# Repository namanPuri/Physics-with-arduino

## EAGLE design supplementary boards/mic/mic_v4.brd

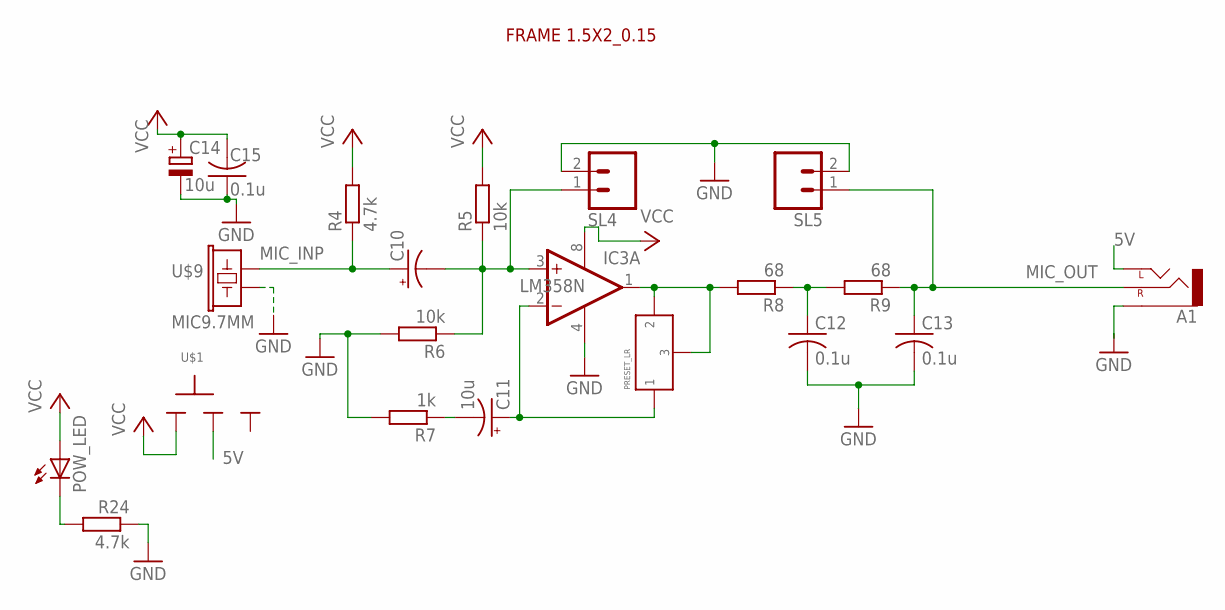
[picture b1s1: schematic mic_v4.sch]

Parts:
A1: AUX-CONNECTOR_CEDT_JANUARY_2015_V5_AUDIO-JACKPTH; AUX-CONNECTOR_CEDT_JANUARY_2015_V5_AUDIO-JACK
C10: CPOL-USE2.5-5; E2,5-5
C11, C14: 10u; E2,5-5
C12, C13, C15: 0.1u; C025-024X044
IC3: LM358N; DIL08
POW_LED: LED3MM
R4, R24: 4.7k; 0204/7
R5, R6: 10k; 0204/7
R7: 1k; 0204/7
R8, R9: 68; 0204/7
SL4, SL5: M02; 02P
U$1: SLIDESWITCH-BIG; BIGSWITCH
U$2: FRAME_1.5X2_RAD_0.15
U$6: PRESET_LR
U$9: MIC9.7MM; MIC-9.7MM

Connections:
5V: A1.TIP (LEFT), U$1.2
GND: A1.SLEEVE, C12.2, C13.2, C14.-, C15.1, IC3.4 (V-), R6.2, R7.2, R24.1, SL4.2, SL5.2, U$9.2
MIC_INP: C10.+, R4.1, U$9.1
MIC_OUT: A1.RING (RIGHT), C13.1, R9.1, SL5.1
unnamed: IC3.1 (OUT), R8.2, U$6.P$2 (2), U$6.P$3 (3)
unnamed: C12.1, R8.1, R9.2
unnamed: C11.-, R7.1
unnamed: POW_LED.K (C), R24.2
unnamed: C10.-, IC3.3 (+IN), R5.1, R6.1, SL4.1
unnamed: C11.+, IC3.2 (-IN), U$6.P$1 (1)
VCC: C14.+, C15.2, IC3.8 (V+), POW_LED.A, R4.2, R5.2, U$1.1

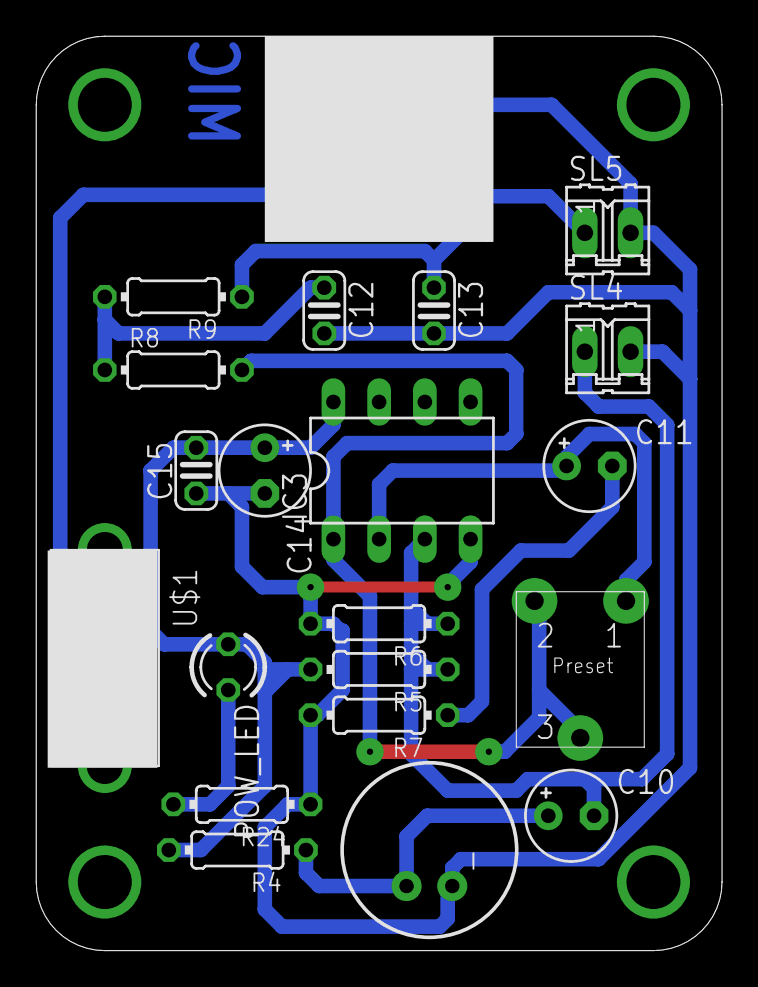
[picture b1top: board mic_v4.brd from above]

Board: 2 copper layers, 38.1 x 50.8 mm, 22 parts (0 on the bottom side), 11 nets.

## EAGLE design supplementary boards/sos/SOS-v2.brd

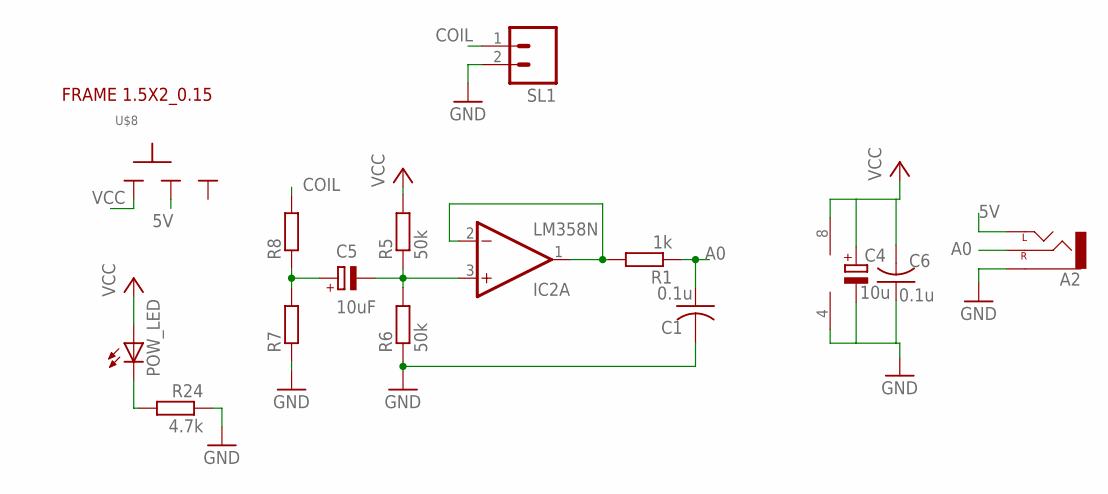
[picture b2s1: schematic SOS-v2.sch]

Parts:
A2: AUX-CONNECTOR_CEDT_JANUARY_2015_V5_AUDIO-JACKPTH; AUX-CONNECTOR_CEDT_JANUARY_2015_V5_AUDIO-JACK
C1, C6: 0.1u; C025-024X044
C4: 10u; E2,5-5
C5: 10uF; E2,5-6
IC2: LM358N; DIL08
POW_LED: LED3MM
R1: 1k; 0204/7
R5, R6: 50k; 0204/7
R7, R8: R-EU_0204/7; 0204/7
R24: 4.7k; 0204/7
SL1: M02; 02P
U$1: FRAME_1.5X2_RAD_0.15
U$8: SLIDESWITCH-BIG; BIGSWITCH

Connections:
5V: A2.TIP (LEFT), U$8.2
A0: A2.RING (RIGHT), C1.1, R1.1
CLAMP_SIGNAL: C5.-, IC2.3 (+IN), R5.1, R6.2
COIL: R8.2, SL1.1
GND: A2.SLEEVE, C1.2, C4.-, C6.1, IC2.4 (V-), R6.1, R7.1, R24.1, SL1.2
unnamed: C5.+, R7.2, R8.1
unnamed: IC2.1 (OUT), IC2.2 (-IN), R1.2
unnamed: POW_LED.K (C), R24.2
VCC: C4.+, C6.2, IC2.8 (V+), POW_LED.A, R5.2, U$8.1

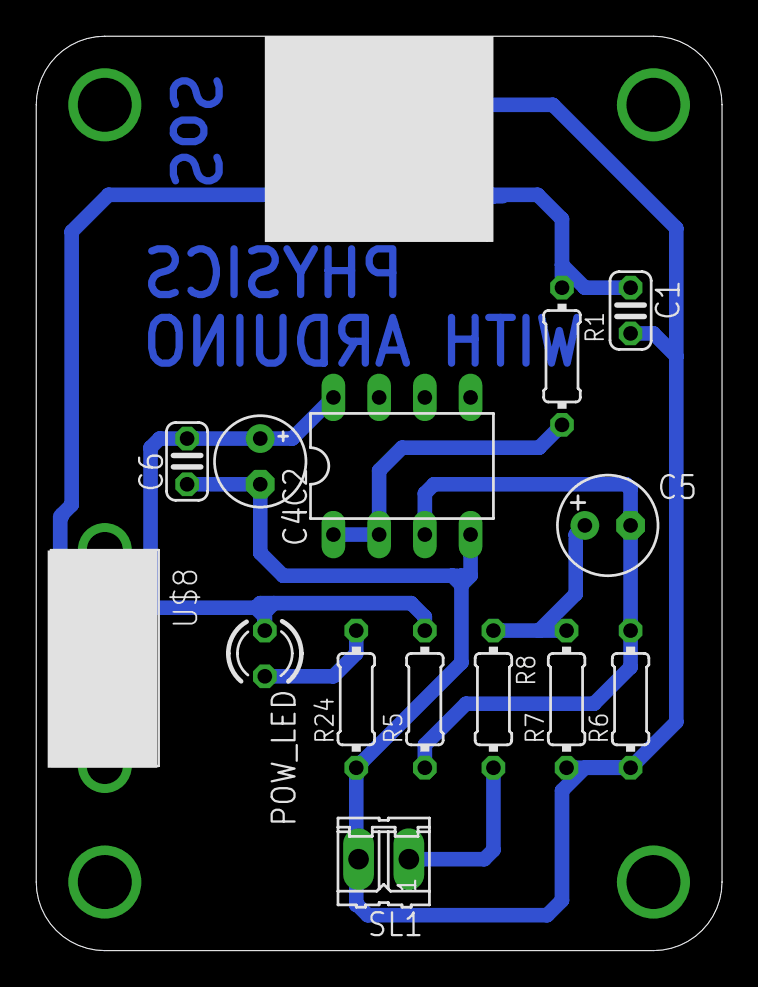
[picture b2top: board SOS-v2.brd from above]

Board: 2 copper layers, 38.1 x 50.8 mm, 16 parts (0 on the bottom side), 9 nets.

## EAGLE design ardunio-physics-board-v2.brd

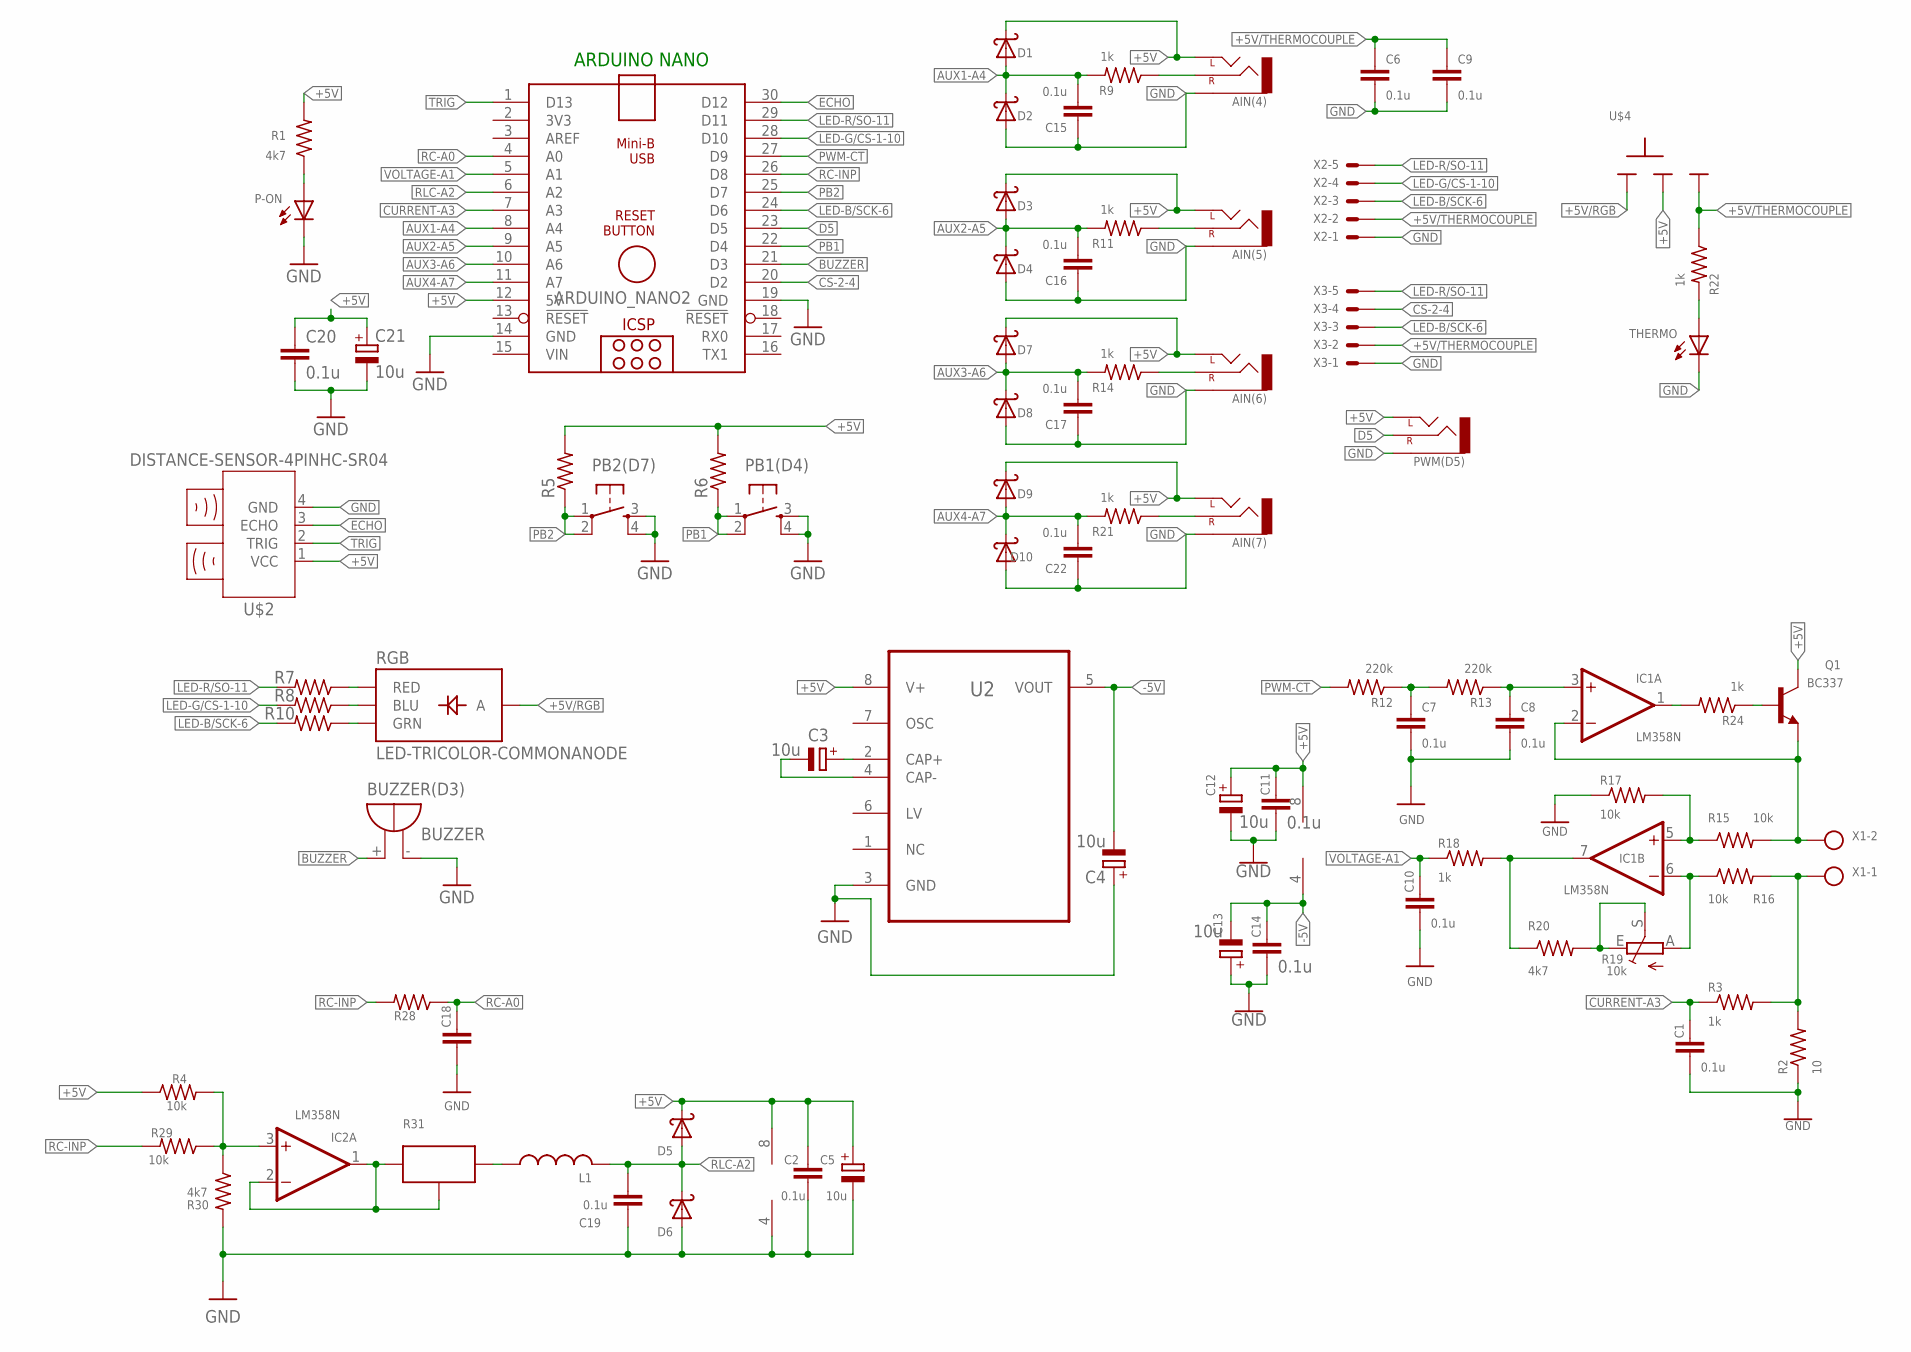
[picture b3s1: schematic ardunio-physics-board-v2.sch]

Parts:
AIN(4), AIN(5), AIN(6), AIN(7): AUX-CONNECTOR_CEDT_JANUARY_2015_V5_AUDIO-JACKPTH; AUX-CONNECTOR_CEDT_JANUARY_2015_V5_AUDIO-JACK
ARDUINO_NANO2: ARDUINONANOV30_ARDUINO_NANO
BUZZER(D3): BUZZER; F/TMB
C1, C2, C7, C8, C10, C11, C14, C19: 0.1u; C025-025X050
C3, C4, C5, C12, C13: 10u; TT2D5
C6, C9, C15, C16, C17, C20, C22: 0.1u; C025-024X044
C18: C-EU025-025X050; C025-025X050
C21: 10u; E2,5-5
D1, D2, D3, D4, D5, D6, D7, D8, D9, D10: 1N5819; DO41-10
IC1, IC2: LM358N; DIL08
L1: L-US6000-XXX-RC; 6000-XXXX-RC
P-ON: LED3MM
PB1(D4), PB2(D7): OMRON_SWITCH_40-XX; B3F-40XX
PWM(D5): AUX-CONNECTOR_CEDT_JANUARY_2015_V5_AUDIO-JACKPTH; AUX-CONNECTOR_CEDT_JANUARY_2015_V5_AUDIO-JACK
Q1: BC337; TO92
R1, R20: 4k7; 0204/7
R2: 10; 0207/10
R3, R9, R11, R14, R18, R21, R22, R24: 1k; 0204/7
R4: 10k; 0207/10
R5, R6: R-US_0204/7; 0204/7
R7, R8, R10, R28: R-US_0207/10; 0207/10
R12: 220k; 0207/10
R13: 220k; 0204/7
R15, R16, R17, R29: 10k; 0204/7
R19: 10k; RJ9W
R30: 4k7; 0207/10
R31: POTNORMAL; RJ9W
RGB: LED-TRICOLOR-COMMONANODE; LED-TRICOLOR-THROUGHHOLE
THERMO: LED3MM
U2: ICL7660CPAZ_ICL7660CPAZ; ICL7660CPAZ_DIP254P762X533-8
U$2: DISTANCE-SENSOR-4PINHC-SR04; HC-SR04
U$4: SLIDESWITCH-BIG; BIGSWITCH
X1: AK500/2-H
X2, X3: JST-XH-05-PIN-LONG-PAD; JST-XH-05-PACKAGE-LONG-PAD

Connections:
+5V: AIN(4).TIP (LEFT), AIN(5).TIP (LEFT), AIN(6).TIP (LEFT), AIN(7).TIP (LEFT), ARDUINO_NANO2.12 (5V), C2.1, C5.+, C11.1, C12.+, C20.1, C21.+, D1.C, D3.C, D5.C, D7.C, D9.C, IC1.8 (V+), IC2.8 (V+), PWM(D5).TIP (LEFT), Q1.3 (C), R1.2, R4.1, R5.2, R6.2, U2.8 (V+), U$2.1 (VCC), U$4.2
+5V/RGB: RGB.ANODE (A), U$4.1
+5V/THERMOCOUPLE: C6.1, C9.1, R22.1, U$4.3, X2.2, X3.2
-5V: C4.-, C13.-, C14.1, IC1.4 (V-), U2.5 (VOUT)
AUX1-A4: ARDUINO_NANO2.8 (A4), C15.2, D1.A, D2.C, R9.2
AUX2-A5: ARDUINO_NANO2.9 (A5), C16.2, D3.A, D4.C, R11.2
AUX3-A6: ARDUINO_NANO2.10 (A6), C17.2, D7.A, D8.C, R14.2
AUX4-A7: ARDUINO_NANO2.11 (A7), C22.2, D9.A, D10.C, R21.2
BUZZER: ARDUINO_NANO2.21 (D3), BUZZER(D3).+
CS-2-4: ARDUINO_NANO2.20 (D2), X3.4
CURRENT-A3: ARDUINO_NANO2.7 (A3), C1.1, R3.1
D5: ARDUINO_NANO2.23 (D5), PWM(D5).RING (RIGHT)
ECHO: ARDUINO_NANO2.30 (D12), U$2.3 (ECHO)
GND: AIN(4).SLEEVE, AIN(5).SLEEVE, AIN(6).SLEEVE, AIN(7).SLEEVE, ARDUINO_NANO2.14 (GND), ARDUINO_NANO2.19 (GND), BUZZER(D3).-, C1.2, C2.2, C4.+, C5.-, C6.2, C7.2, C8.2, C9.2, C10.2, C11.2, C12.-, C13.+, C14.2, C15.1, C16.1, C17.1, C18.2, C19.2, C20.2, C21.-, C22.1, D2.A, D4.A, D6.A, D8.A, D10.A, IC2.4 (V-), P-ON.K (C), PB1(D4).3 (S), PB1(D4).4 (S1), PB2(D7).3 (S), PB2(D7).4 (S1), PWM(D5).SLEEVE, R2.1, R17.1, R30.2, THERMO.K (C), U2.3 (GND), U$2.4 (GND), X2.1, X3.1
LED-B/SCK-6: ARDUINO_NANO2.24 (D6), R10.2, X2.3, X3.3
LED-G/CS-1-10: ARDUINO_NANO2.28 (D10), R8.2, X2.4
LED-R/SO-11: ARDUINO_NANO2.29 (D11), R7.2, X2.5, X3.5
unnamed: IC1.2 (-IN), Q1.1 (E), R15.2, X1.2
unnamed: R7.1, RGB.RED
unnamed: R8.1, RGB.BLU
unnamed: R10.1, RGB.GRN
unnamed: IC1.1 (OUT), R24.2
unnamed: C8.1, IC1.3 (+IN), R13.1
unnamed: IC2.3 (+IN), R4.2, R29.1, R30.1
unnamed: C3.+, U2.2 (CAP+)
unnamed: C3.-, U2.4 (CAP-)
unnamed: C7.1, R12.1, R13.2
unnamed: R2.2, R3.2, R16.2, X1.1
unnamed: P-ON.A, R1.1
unnamed: Q1.2 (B), R24.1
unnamed: IC2.1 (OUT), IC2.2 (-IN), R31.E, R31.S
unnamed: AIN(4).RING (RIGHT), R9.1
unnamed: IC1.5 (+IN), R15.1, R17.2
unnamed: IC1.6 (-IN), R16.1, R19.A
unnamed: R19.E, R19.S, R20.2
unnamed: IC1.7 (OUT), R18.2, R20.1
unnamed: AIN(5).RING (RIGHT), R11.1
unnamed: L1.1, R31.A
unnamed: R22.2, THERMO.A
unnamed: AIN(6).RING (RIGHT), R14.1
unnamed: AIN(7).RING (RIGHT), R21.1
PB1: ARDUINO_NANO2.22 (D4), PB1(D4).1, PB1(D4).2 (P1), R6.1
PB2: ARDUINO_NANO2.25 (D7), PB2(D7).1, PB2(D7).2 (P1), R5.1
PWM-CT: ARDUINO_NANO2.27 (D9), R12.2
RC-A0: ARDUINO_NANO2.4 (A0), C18.1, R28.1
RC-INP: ARDUINO_NANO2.26 (D8), R28.2, R29.2
RLC-A2: ARDUINO_NANO2.6 (A2), C19.1, D5.A, D6.C, L1.2
TRIG: ARDUINO_NANO2.1 (D13), U$2.2 (TRIG)
VIN: ARDUINO_NANO2.15 (VIN)
VOLTAGE-A1: ARDUINO_NANO2.5 (A1), C10.1, R18.1

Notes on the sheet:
ARDUINO NANO

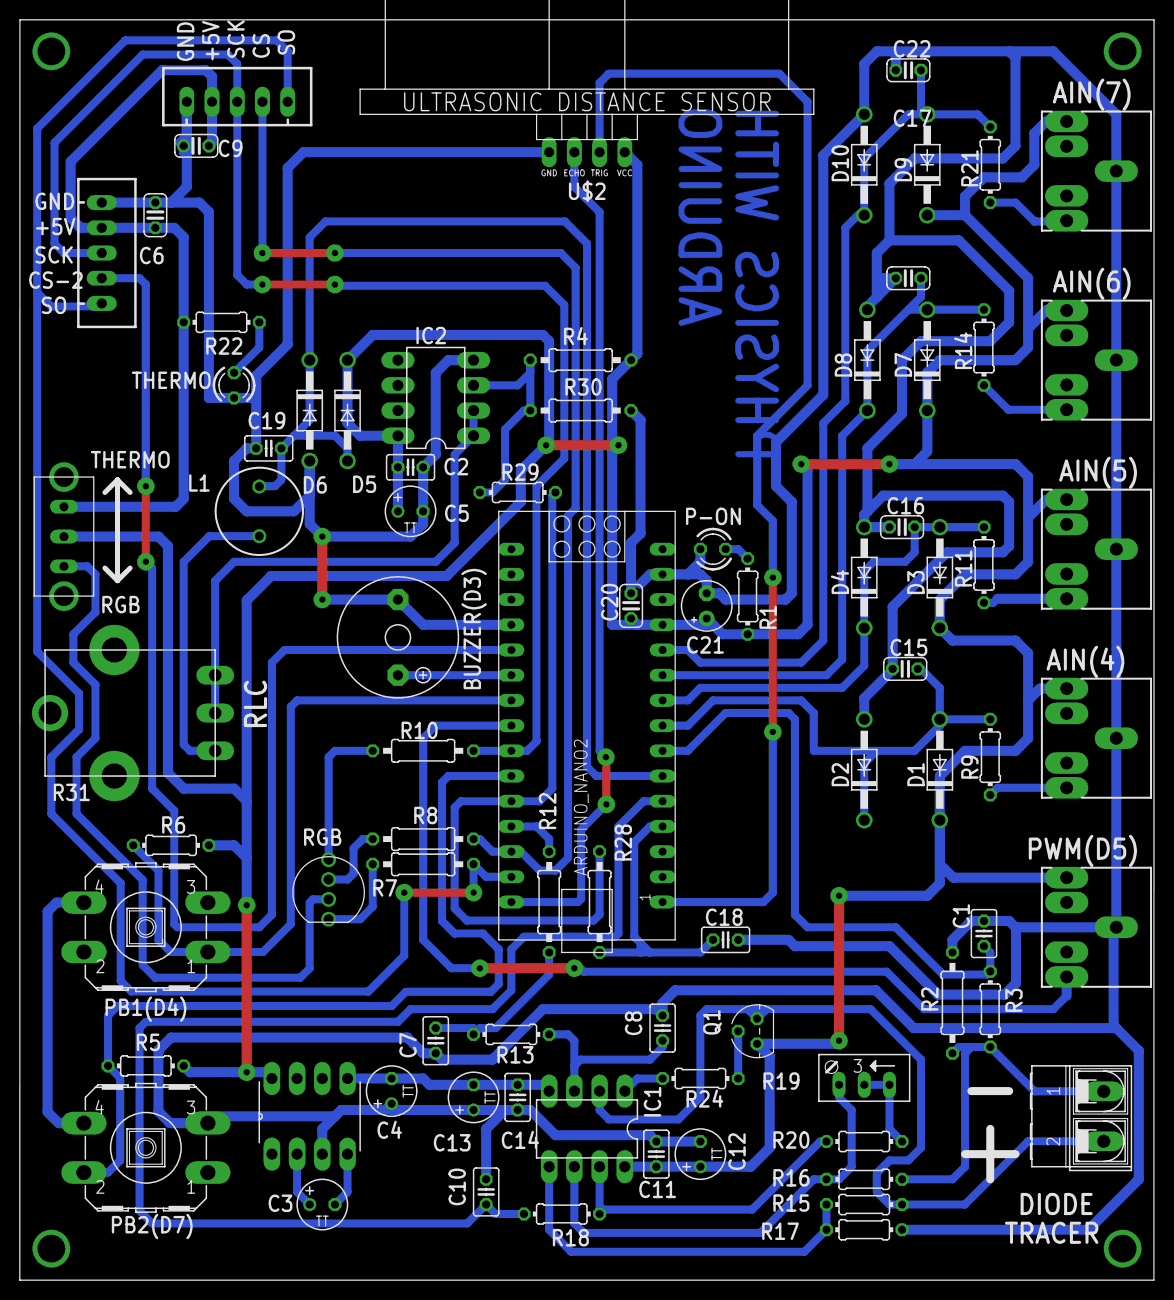
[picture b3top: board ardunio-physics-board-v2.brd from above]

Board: 2 copper layers, 114.3 x 127.0 mm, 81 parts (0 on the bottom side), 49 nets.

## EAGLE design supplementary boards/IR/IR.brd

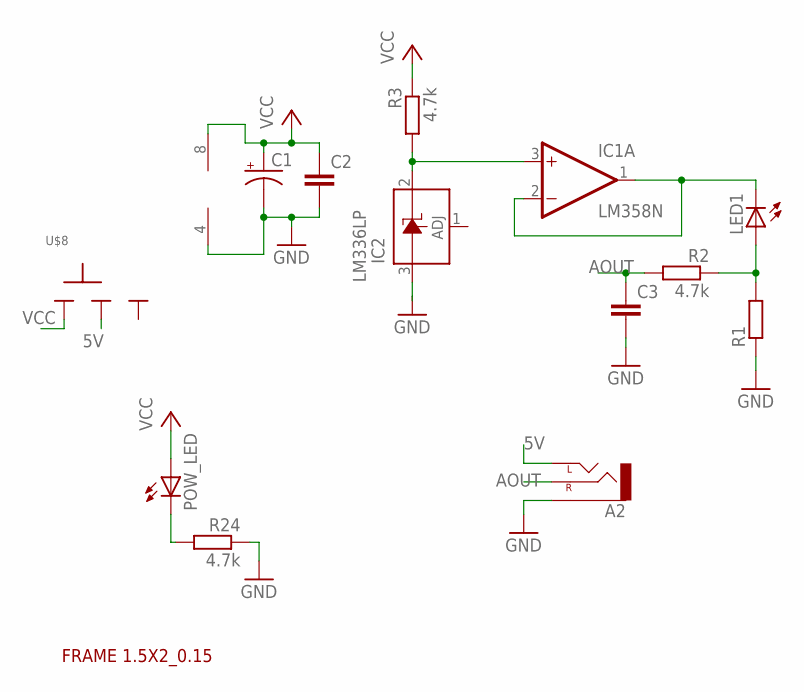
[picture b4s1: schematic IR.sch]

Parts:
A2: AUX-CONNECTOR_CEDT_JANUARY_2015_V5_AUDIO-JACKPTH; AUX-CONNECTOR_CEDT_JANUARY_2015_V5_AUDIO-JACK
C1: CAP_POL; E2,5-5-10U
C2, C3: C-EU025-024X044; C025-024X044
IC1: LM358N; DIL08
IC2: LM336LP; TO92
LED1: LED5MM
POW_LED: LED3MM
R1: R-EU_0204/7; 0204/7
R2, R3, R24: 4.7k; 0204/7
U$1: FRAME_1.5X2_RAD_0.15
U$8: SLIDESWITCH-BIG; BIGSWITCH

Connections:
5V: A2.TIP (LEFT), U$8.2
AOUT: A2.RING (RIGHT), C3.1, R2.2
GND: A2.SLEEVE, C1.-, C2.2, C3.2, IC1.4 (V-), IC2.3 (A), R1.1, R24.1
unnamed: IC1.3 (+IN), IC2.2 (C), R3.2
unnamed: LED1.A, R1.2, R2.1
unnamed: IC1.1 (OUT), IC1.2 (-IN), LED1.K (C)
unnamed: POW_LED.K (C), R24.2
VCC: C1.+, C2.1, IC1.8 (V+), POW_LED.A, R3.1, U$8.1

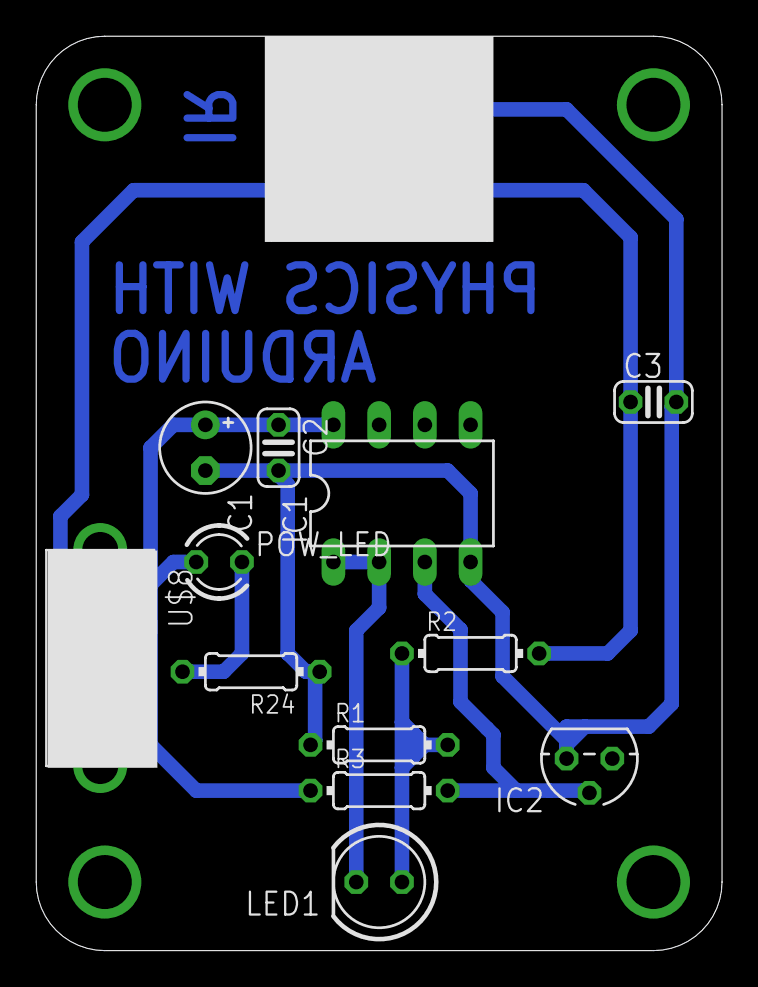
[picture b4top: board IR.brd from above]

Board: 2 copper layers, 38.1 x 50.8 mm, 14 parts (0 on the bottom side), 8 nets.

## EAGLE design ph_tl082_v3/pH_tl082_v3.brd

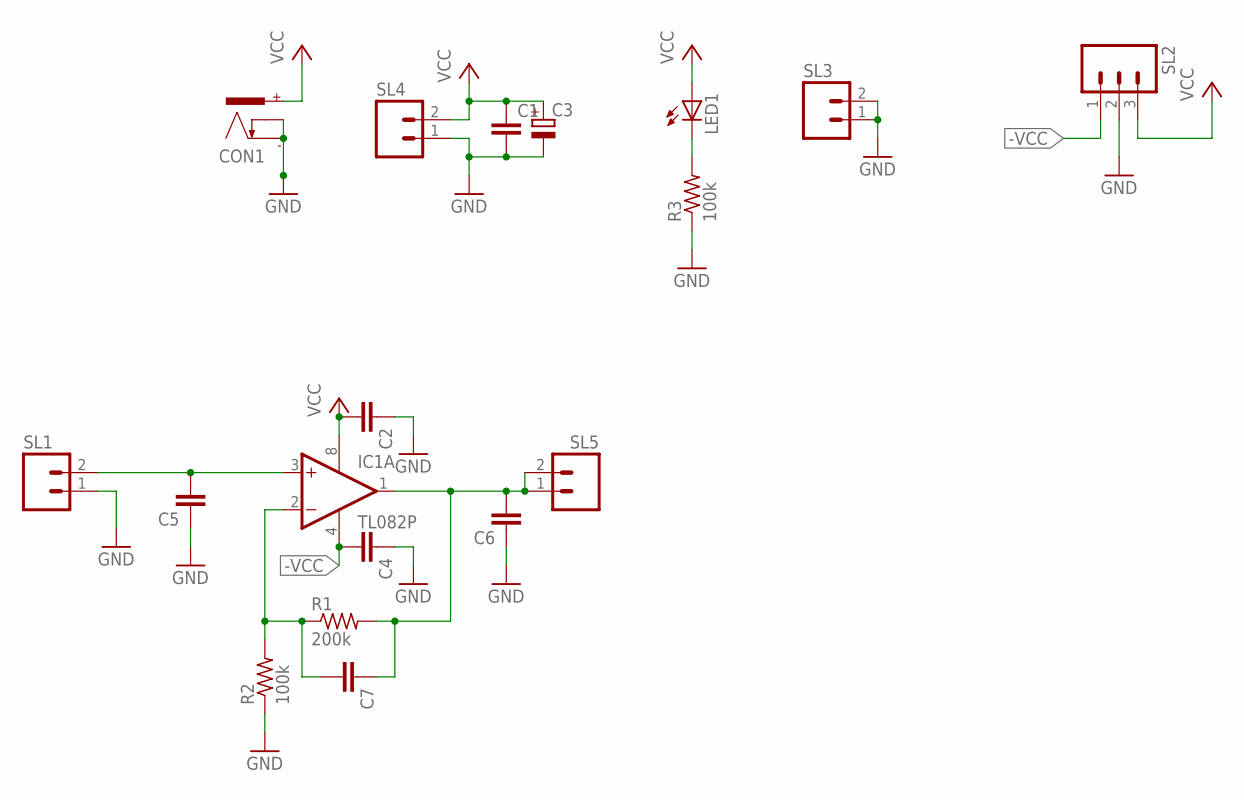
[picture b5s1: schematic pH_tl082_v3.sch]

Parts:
C1, C2, C4, C5, C6, C7: C2.5/2; C2.5-2
C3: CPOL-EUE2,5-6E; E2,5-6E
CON1: POWER_CON; NEB21R
IC1: TL082P; DIL08
LED1: LED3MM
R1: 200k; 0207/7
R2, R3: 100k; 0207/7
SL1, SL3, SL4, SL5: M02; 02P
SL2: M03; 03P

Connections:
-VCC: C4.2, IC1.4 (V-), SL2.1
GND: C1.2, C2.1, C3.-, C4.1, C5.1, C6.1, CON1.-, CON1.C, R2.1, R3.1, SL1.1, SL2.2, SL3.1, SL3.2, SL4.1
unnamed: C5.2, IC1.3 (+IN), SL1.2
unnamed: C7.2, IC1.2 (-IN), R1.1, R2.2
unnamed: C6.2, C7.1, IC1.1 (OUT), R1.2, SL5.1, SL5.2
unnamed: LED1.K (C), R3.2
VCC: C1.1, C2.2, C3.+, CON1.+, IC1.8 (V+), LED1.A, SL2.3, SL4.2

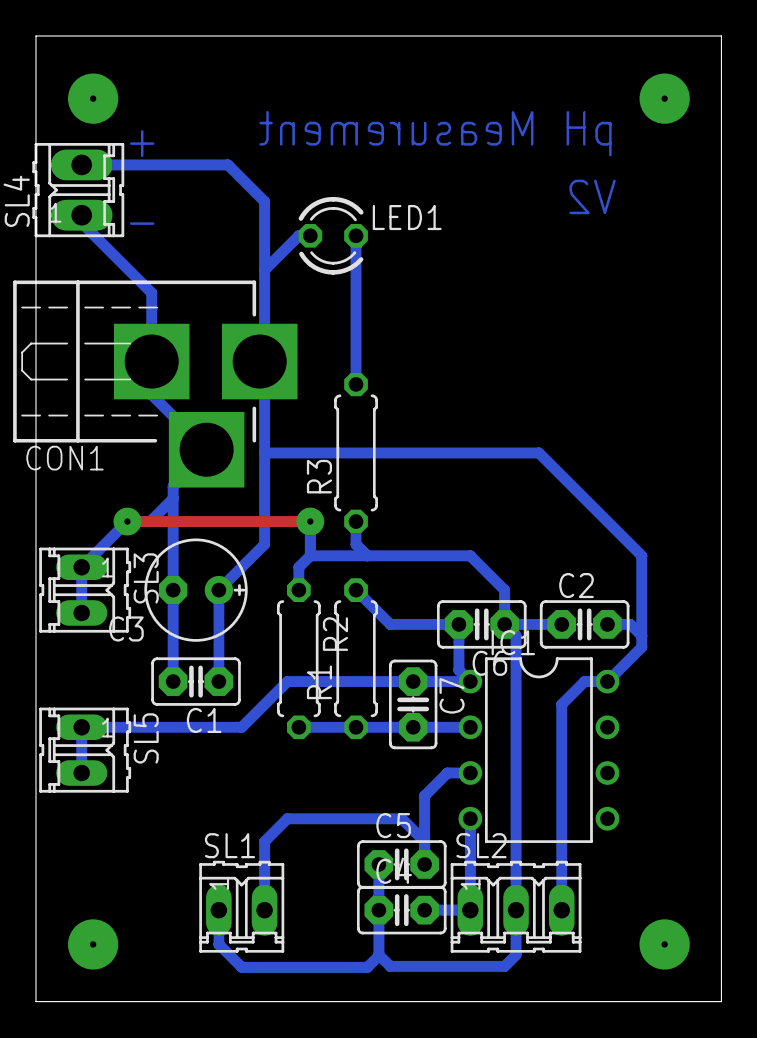
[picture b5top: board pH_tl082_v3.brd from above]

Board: 2 copper layers, 38.1 x 53.6 mm, 18 parts (0 on the bottom side), 7 nets.

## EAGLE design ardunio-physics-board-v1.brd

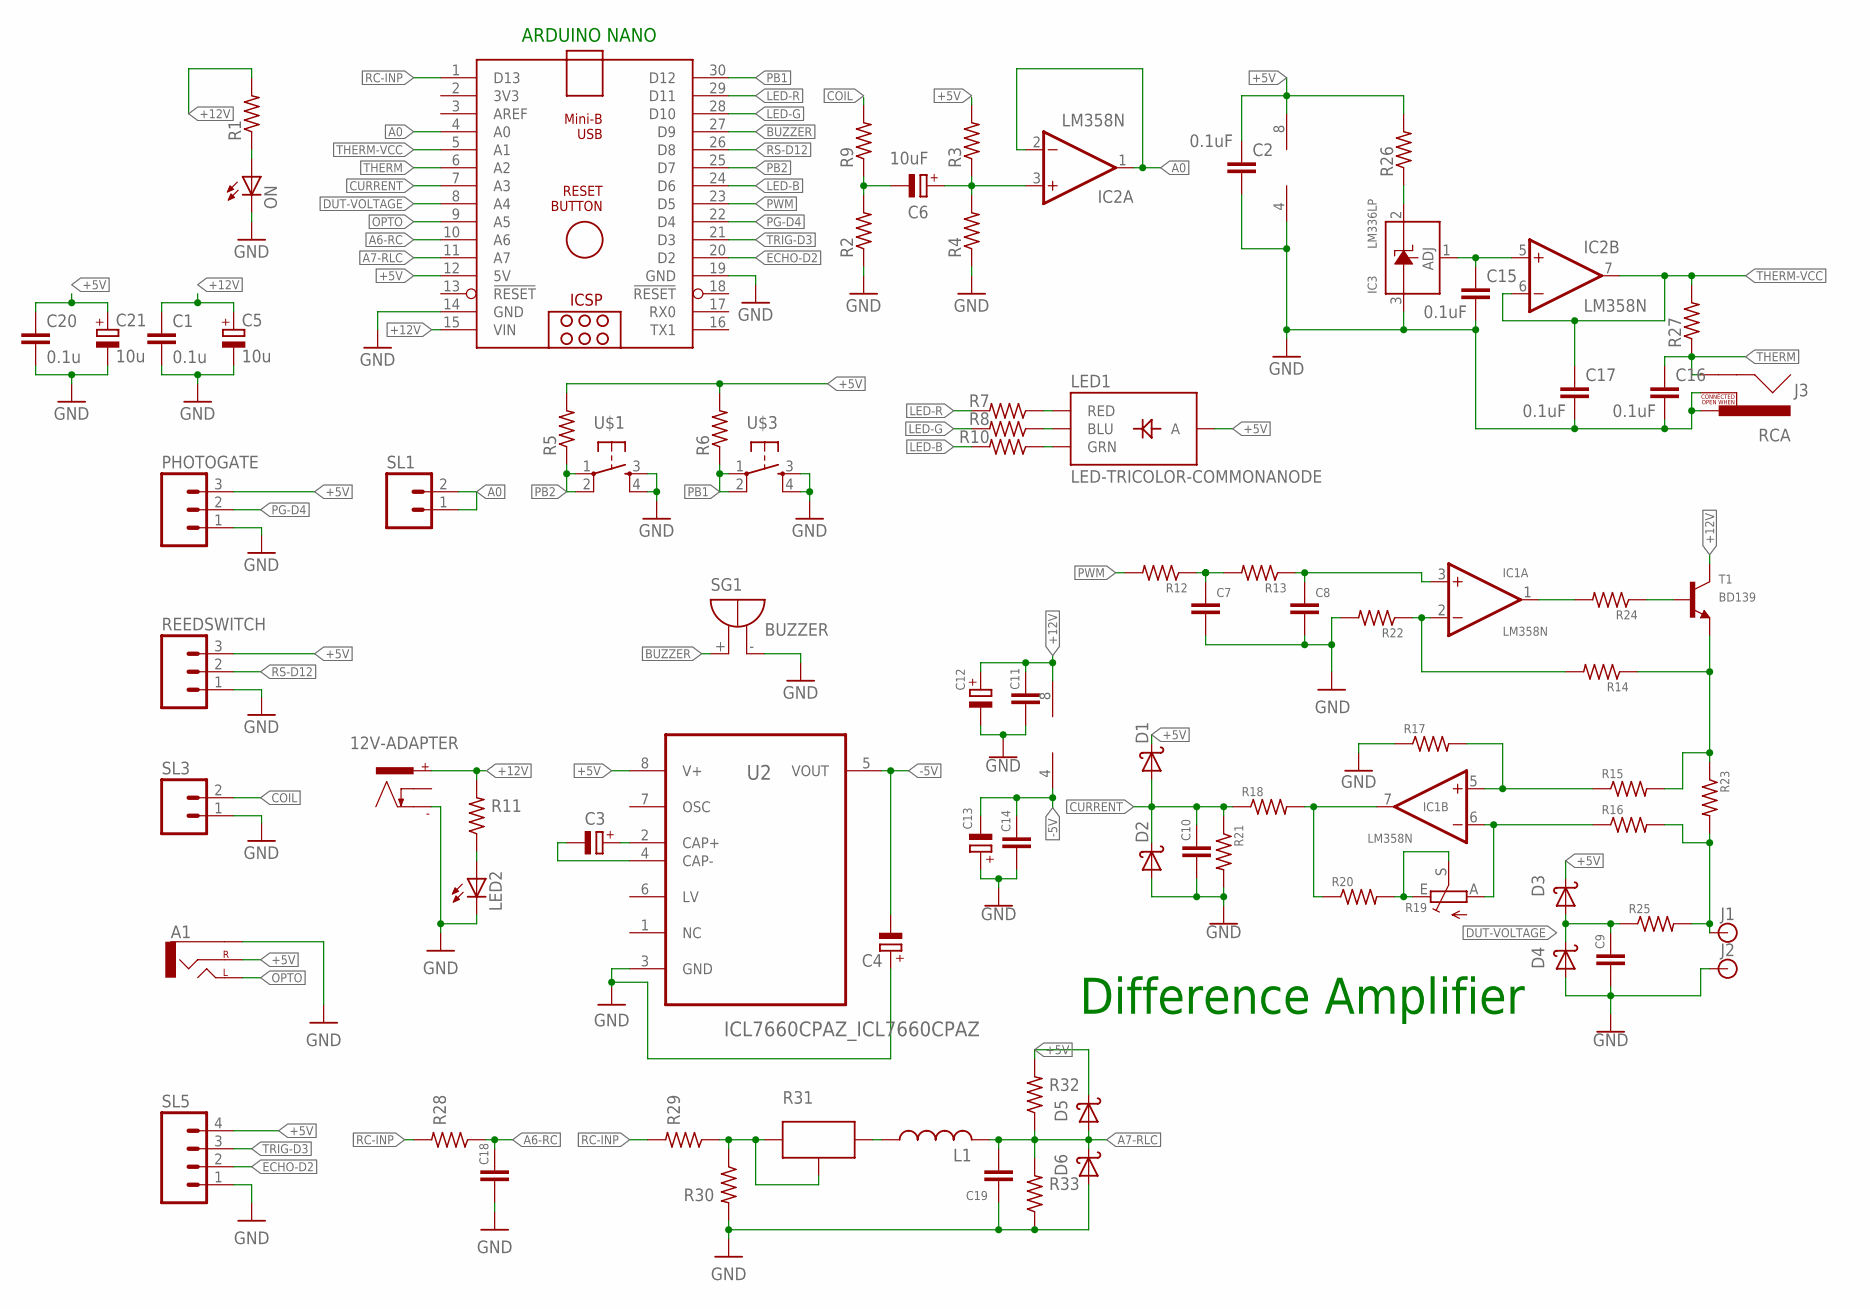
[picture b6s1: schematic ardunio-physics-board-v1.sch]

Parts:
12V-ADAPTER: POWER_CON; NEB21R
A1: CEDT_JANUARY_2015_V5_AUDIO-JACKPTH; CEDT_JANUARY_2015_V5_AUDIO-JACK
ARDUINO_NANO1: ARDUINO_NANO
C1, C20: 0.1u; C025-024X044
C2, C15, C16, C17: 0.1uF; C025-025X050
C3, C4, C12, C13: CPOL-EUTT2D5; TT2D5
C5, C21: 10u; E2,5-5
C6: 10uF; E2,5-6
C7, C8, C9, C10, C11, C14, C18, C19: C-EU025-025X050; C025-025X050
D1, D2, D3, D4, D5, D6: 1N5819; DO41-10
IC1, IC2: LM358N; DIL08
IC3: LM336LP; TO92
J1, J2: BANANA_CONN
J3: RCA
L1: L-US6000-XXX-RC; 6000-XXXX-RC
LED1: LED-TRICOLOR-COMMONANODE; LED-TRICOLOR-THROUGHHOLE
LED2: LED3MM
ON: LED3MM
PHOTOGATE: M03; 03P
R1, R2, R3, R4, R5, R6, R7, R8, R9, R10, R11, R12, R13, R14, R15, R16, R17, R18, R20, R21, R22, R24, R25, R26, R27, R28, R29, R30, R32, R33: R-US_0204/7; 0204/7
R19: TRIM_EU-RJ9W; RJ9W
R23: R-US_0207/10; 0207/10
R31: POTNORMAL; RJ9W
REEDSWITCH: M03; 03P
SG1: BUZZER; F/TMB
SL1, SL3: M02; 02P
SL5: M04; 04P
T1: BD139; TO126
U2: ICL7660CPAZ_ICL7660CPAZ; ICL7660CPAZ_DIP254P762X533-8
U$1, U$3: OMRON_SWITCH_40-XX; B3F-40XX

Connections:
+5V: A1.RING (RIGHT), ARDUINO_NANO1.12 (5V), C2.1, C20.1, C21.+, D1.C, D3.C, D5.C, IC2.8 (V+), LED1.ANODE (A), PHOTOGATE.3, R3.2, R5.2, R6.2, R26.2, R32.2, REEDSWITCH.3, SL5.4, U2.8 (V+)
+12V: 12V-ADAPTER.+, ARDUINO_NANO1.15 (VIN), C1.1, C5.+, C11.1, C12.+, IC1.8 (V+), R1.2, R11.2, T1.2 (C)
-5V: C4.-, C13.-, C14.1, IC1.4 (V-), U2.5 (VOUT)
A0: ARDUINO_NANO1.4 (A0), IC2.1 (OUT), IC2.2 (-IN), SL1.1, SL1.2
A6-RC: ARDUINO_NANO1.10 (A6), C18.1, R28.1
A7-RLC: ARDUINO_NANO1.11 (A7), C19.1, D5.A, D6.C, L1.2, R32.1, R33.2
BUZZER: ARDUINO_NANO1.27 (D9), SG1.+
CLAMP_SIGNAL: C6.+, IC2.3 (+IN), R3.1, R4.2
COIL: R9.2, SL3.2
CURRENT: ARDUINO_NANO1.7 (A3), C10.1, D1.A, D2.C, R18.1, R21.1
DUT-VOLTAGE: ARDUINO_NANO1.8 (A4), C9.1, D3.A, D4.C, R25.1
ECHO-D2: ARDUINO_NANO1.20 (D2), SL5.2
GND: 12V-ADAPTER.-, A1.SLEEVE, ARDUINO_NANO1.14 (GND), ARDUINO_NANO1.19 (GND), C1.2, C2.2, C4.+, C5.-, C7.2, C8.2, C9.2, C10.2, C11.2, C12.-, C13.+, C14.2, C15.2, C16.2, C17.2, C18.2, C19.2, C20.2, C21.-, D2.A, D4.A, D6.A, IC2.4 (V-), IC3.3 (A), J2.P$1, J3.PIN, J3.SWITCH, LED2.K (C), ON.K (C), PHOTOGATE.1, R2.1, R4.1, R17.1, R21.2, R22.2, R30.2, R33.1, REEDSWITCH.1, SG1.-, SL3.1, SL5.1, U2.3 (GND), U$1.3 (S), U$1.4 (S1), U$3.3 (S), U$3.4 (S1)
LED-B: ARDUINO_NANO1.24 (D6), R10.2
LED-G: ARDUINO_NANO1.28 (D10), R8.2
LED-R: ARDUINO_NANO1.29 (D11), R7.2
unnamed: C6.-, R2.2, R9.1
unnamed: LED1.RED, R7.1
unnamed: LED1.BLU, R8.1
unnamed: LED1.GRN, R10.1
unnamed: IC1.1 (OUT), R24.2
unnamed: IC3.2 (C), R26.1
unnamed: C15.1, IC2.5 (+IN), IC3.1 (ADJ)
unnamed: C3.+, U2.2 (CAP+)
unnamed: C3.-, U2.4 (CAP-)
unnamed: C7.1, R12.1, R13.2
unnamed: LED2.A, R11.1
unnamed: ON.A, R1.1
unnamed: R24.1, T1.3 (B)
unnamed: C8.1, IC1.3 (+IN), R13.1
unnamed: IC1.2 (-IN), R14.2, R22.1
unnamed: IC1.5 (+IN), R15.1, R17.2
unnamed: IC1.6 (-IN), R16.1, R19.A
unnamed: R14.1, R15.2, R23.1, T1.1 (E)
unnamed: R19.E, R19.S, R20.2
unnamed: IC1.7 (OUT), R18.2, R20.1
unnamed: J1.P$1, R16.2, R23.2, R25.2
unnamed: R29.1, R30.1, R31.E, R31.S
unnamed: L1.1, R31.A
OPTO: A1.TIP (LEFT), ARDUINO_NANO1.9 (A5)
PB1: ARDUINO_NANO1.30 (D12), R6.1, U$3.1, U$3.2 (P1)
PB2: ARDUINO_NANO1.25 (D7), R5.1, U$1.1, U$1.2 (P1)
PG-D4: ARDUINO_NANO1.22 (D4), PHOTOGATE.2
PWM: ARDUINO_NANO1.23 (D5), R12.2
RC-INP: ARDUINO_NANO1.1 (D13), R28.2, R29.2
RS-D12: ARDUINO_NANO1.26 (D8), REEDSWITCH.2
THERM: ARDUINO_NANO1.6 (A2), C16.1, J3.SHELL, R27.1
THERM-VCC: ARDUINO_NANO1.5 (A1), C17.1, IC2.6 (-IN), IC2.7 (OUT), R27.2
TRIG-D3: ARDUINO_NANO1.21 (D3), SL5.3

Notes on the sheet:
ARDUINO NANO
Difference Amplifier

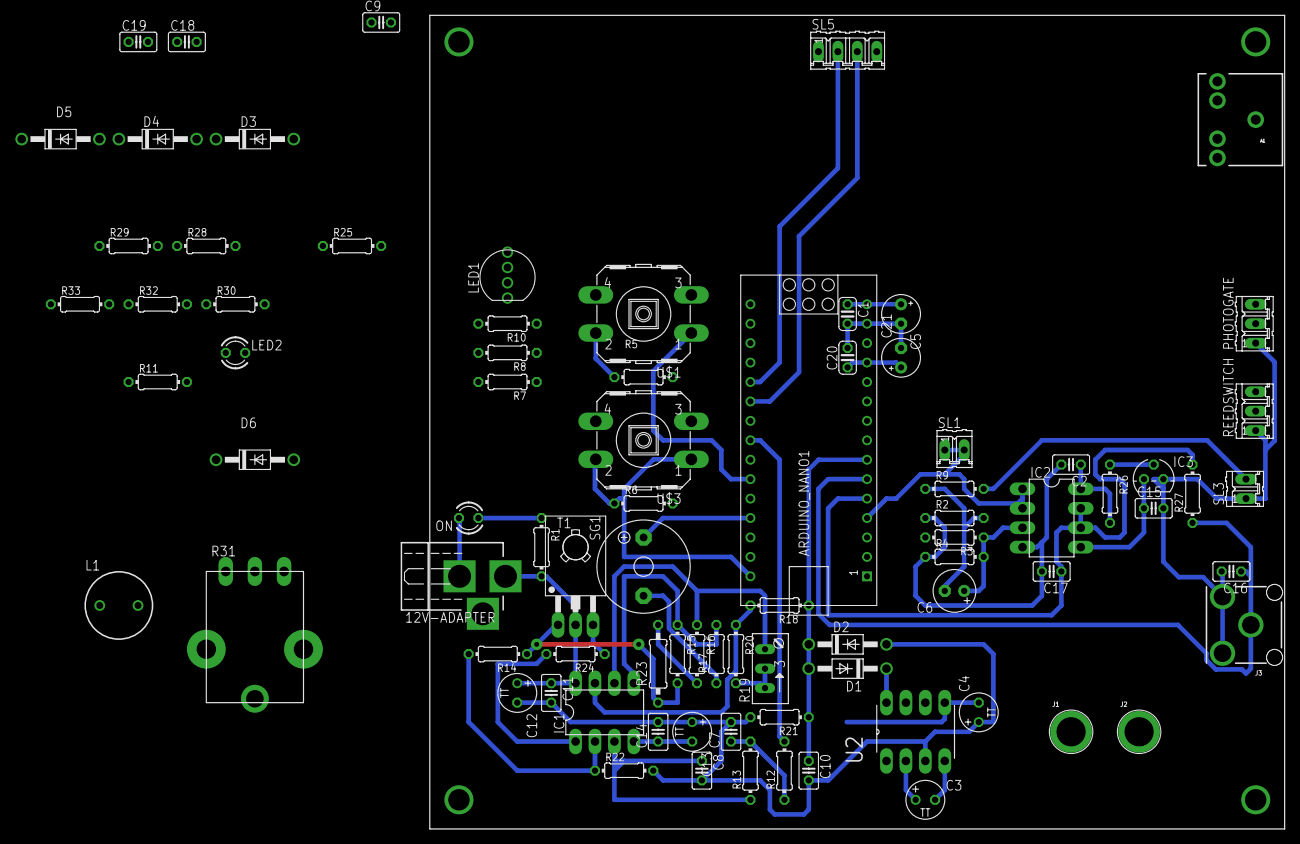
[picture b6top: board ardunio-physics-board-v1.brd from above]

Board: 2 copper layers, 111.7 x 106.3 mm, 83 parts (0 on the bottom side), 49 nets.

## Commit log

2022-06-27 27-06-2022

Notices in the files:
parts and their libraries:
SparkFun-Connectors: Licensing: Creative Commons ShareAlike 4.0 International - https://creativecommons.org/licenses/by-sa/4.0
